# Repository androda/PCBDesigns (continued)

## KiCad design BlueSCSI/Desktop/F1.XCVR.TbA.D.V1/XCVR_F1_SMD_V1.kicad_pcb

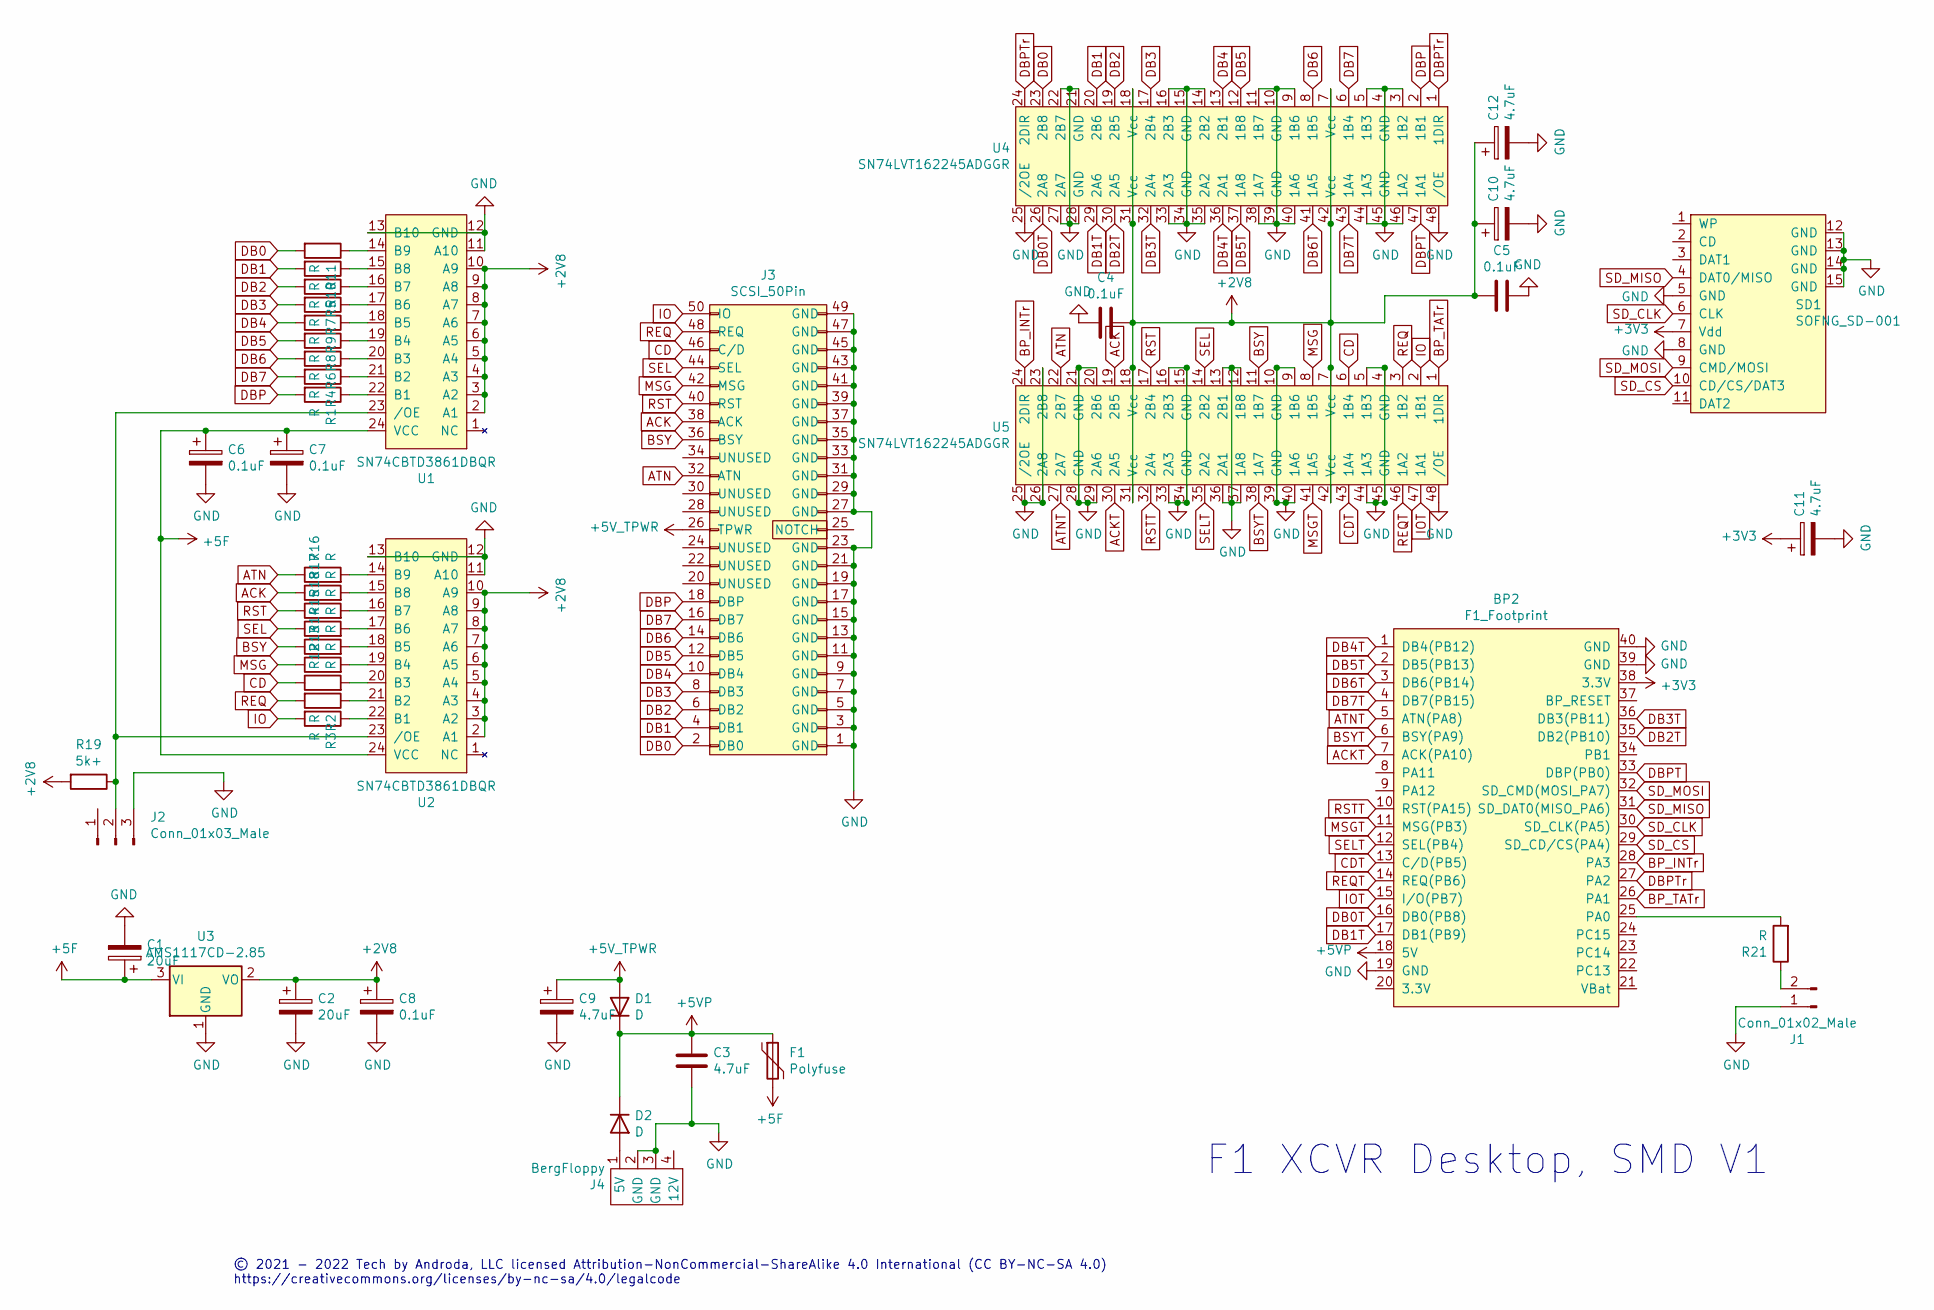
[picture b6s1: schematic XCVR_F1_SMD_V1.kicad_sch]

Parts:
BP2: F1_Footprint; BluePillModule
C1, C2: 20uF; C_1206_3216Metric_Pad1.42x1.75mm_HandSolder
C3, C9, C10, C11, C12: 4.7uF; C_0805_2012Metric_Pad1.15x1.40mm_HandSolder
C4, C5, C6, C7, C8: 0.1uF; C_0805_2012Metric_Pad1.15x1.40mm_HandSolder
D1, D2: D; D_SMA
F1: Polyfuse; Fuse_BelFuse_0ZRE0005FF_L8.3mm_W3.8mm
J1: Conn_01x02_Male; PinHeader_1x02_P2.54mm_Vertical
J2: Conn_01x03_Male; PinHeader_1x03_P2.54mm_Vertical
J3: SCSI_50Pin; SCSI50_EdgeConn
J4: BergFloppy; BergFloppy_RightAngle
R1, R2, R3, R4, R5, R6, R7, R8, R9, R10, R11, R12, R13, R14, R15, R16, R17, R18: R; R_0603_1608Metric_Pad1.05x0.95mm_HandSolder
R19: 5k+; R_0805_2012Metric_Pad1.15x1.40mm_HandSolder
R21: R; R_0805_2012Metric_Pad1.15x1.40mm_HandSolder
SD1: SOFNG_SD-001
U1, U2: SN74CBTD3861DBQR; SSOP-24_3.9x8.7mm_P0.635mm
U3: AMS1117CD-2.85; SOT-223-3_TabPin2
U4, U5: SN74LVT162245ADGGR; TSSOP-48_6.1x12.5mm_P0.5mm

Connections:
+2V8: C2.1, C4.1, C5.1, C8.1, C10.1, C12.1, R19.2, U1.2 (A1), U1.3 (A2), U1.4 (A3), U1.5 (A4), U1.6 (A5), U1.7 (A6), U1.8 (A7), U1.9 (A8), U1.10 (A9), U2.2 (A1), U2.3 (A2), U2.4 (A3), U2.5 (A4), U2.6 (A5), U2.7 (A6), U2.8 (A7), U2.9 (A8), U2.10 (A9), U3.2 (VO), U4.7 (Vcc), U4.18 (Vcc), U4.31 (Vcc), U4.42 (Vcc), U5.7 (Vcc), U5.18 (Vcc), U5.31 (Vcc), U5.42 (Vcc)
+3V3: BP2.38 (3.3V), C11.1, SD1.7 (Vdd)
+5F: C1.1, C6.1, C7.1, F1.2, U1.24 (VCC), U2.24 (VCC), U3.3 (VI)
+5V: C9.1, D1.2 (A), J3.26 (TPWR)
+5VP: BP2.18 (5V), C3.1, D1.1 (K), D2.1 (K), F1.1
ACK: J3.38 (ACK), R17.1, U5.19 (2B5)
ACKT: BP2.7 (ACK(PA10)), U5.30 (2A5)
ATN: J3.32 (ATN), R16.1, U5.22 (2B7)
ATNT: BP2.5 (ATN(PA8)), U5.27 (2A7)
BP_INTr: BP2.28 (PA3), U5.24 (2DIR)
BP_TATr: BP2.26 (PA1), U5.1 (1DIR)
BSY: J3.36 (BSY), R14.1, U5.11 (1B7)
BSYT: BP2.6 (BSY(PA9)), U5.38 (1A7)
CD: J3.46 (C/D), R12.1, U5.6 (1B4)
CDT: BP2.13 (C/D(PB5)), U5.43 (1A4)
DB0: J3.2 (DB0), R11.2, U4.23 (2B8)
DB0T: BP2.16 (DB0(PB8)), U4.26 (2A8)
DB1: J3.4 (DB1), R10.2, U4.20 (2B6)
DB1T: BP2.17 (DB1(PB9)), U4.29 (2A6)
DB2: J3.6 (DB2), R5.2, U4.19 (2B5)
DB2T: BP2.35 (DB2(PB10)), U4.30 (2A5)
DB3: J3.8 (DB3), R7.2, U4.17 (2B4)
DB3T: BP2.36 (DB3(PB11)), U4.32 (2A4)
DB4: J3.10 (DB4), R9.2, U4.13 (2B1)
DB4T: BP2.1 (DB4(PB12)), U4.36 (2A1)
DB5: J3.12 (DB5), R8.2, U4.12 (1B8)
DB5T: BP2.2 (DB5(PB13)), U4.37 (1A8)
DB6: J3.14 (DB6), R6.2, U4.8 (1B5)
DB6T: BP2.3 (DB6(PB14)), U4.41 (1A5)
DB7: J3.16 (DB7), R4.2, U4.6 (1B4)
DB7T: BP2.4 (DB7(PB15)), U4.43 (1A4)
DBP: J3.18 (DBP), R1.2, U4.2 (1B1)
DBPT: BP2.33 (DBP(PB0)), U4.47 (1A1)
DBPTr: BP2.27 (PA2), U4.1 (1DIR), U4.24 (2DIR)
GND: BP2.19 (GND), BP2.39 (GND), BP2.40 (GND), C1.2, C2.2, C3.2, C4.2, C5.2, C6.2, C7.2, C8.2, C9.2, C10.2, C11.2, C12.2, J1.1, J2.3, J3.1 (GND), J3.3 (GND), J3.5 (GND), J3.7 (GND), J3.9 (GND), J3.11 (GND), J3.13 (GND), J3.15 (GND), J3.17 (GND), J3.19 (GND), J3.21 (GND), J3.23 (GND), J3.27 (GND), J3.29 (GND), J3.31 (GND), J3.33 (GND), J3.35 (GND), J3.37 (GND), J3.39 (GND), J3.41 (GND), J3.43 (GND), J3.45 (GND), J3.47 (GND), J3.49 (GND), J4.2 (GND), J4.3 (GND), SD1.5 (GND), SD1.8 (GND), SD1.12 (GND), SD1.13 (GND), SD1.14 (GND), SD1.15 (GND), U1.11 (A10), U1.12 (GND), U1.13 (B10), U2.11 (A10), U2.12 (GND), U2.13 (B10), U3.1 (GND), U4.3 (1B2), U4.4 (GND), U4.5 (1B3), U4.9 (1B6), U4.10 (GND), U4.11 (1B7), U4.14 (2B2), U4.15 (GND), U4.16 (2B3), U4.21 (GND), U4.22 (2B7), U4.25 (/2OE), U4.27 (2A7), U4.28 (GND), U4.33 (2A3), U4.34 (GND), U4.35 (2A2), U4.38 (1A7), U4.39 (GND), U4.40 (1A6), U4.44 (1A3), U4.45 (GND), U4.46 (1A2), U4.48 (/OE), U5.4 (GND), U5.5 (1B3), U5.9 (1B6), U5.10 (GND), U5.12 (1B8), U5.13 (2B1), U5.15 (GND), U5.16 (2B3), U5.20 (2B6), U5.21 (GND), U5.23 (2B8), U5.25 (/2OE), U5.26 (2A8), U5.28 (GND), U5.29 (2A6), U5.33 (2A3), U5.34 (GND), U5.36 (2A1), U5.37 (1A8), U5.39 (GND), U5.40 (1A6), U5.44 (1A3), U5.45 (GND), U5.48 (/OE)
IO: J3.50 (IO), R3.2, U5.2 (1B1)
IOT: BP2.15 (I/O(PB7)), U5.47 (1A1)
MSG: J3.42 (MSG), R13.1, U5.8 (1B5)
MSGT: BP2.11 (MSG(PB3)), U5.41 (1A5)
unnamed: BP2.25 (PA0), R21.2
unnamed: D2.2 (A), J4.1 (5V)
unnamed: J1.2, R21.1
unnamed: J2.2, R19.1, U1.23 (/OE), U2.23 (/OE)
unnamed: R1.1, U1.22 (B1)
unnamed: R2.1, U2.21 (B2)
unnamed: R3.1, U2.22 (B1)
unnamed: R4.1, U1.21 (B2)
unnamed: R5.1, U1.16 (B7)
unnamed: R6.1, U1.20 (B3)
unnamed: R7.1, U1.17 (B6)
unnamed: R8.1, U1.19 (B4)
unnamed: R9.1, U1.18 (B5)
unnamed: R10.1, U1.15 (B8)
unnamed: R11.1, U1.14 (B9)
unnamed: R12.2, U2.20 (B3)
unnamed: R13.2, U2.19 (B4)
unnamed: R14.2, U2.18 (B5)
unnamed: R15.2, U2.17 (B6)
unnamed: R16.2, U2.14 (B9)
unnamed: R17.2, U2.15 (B8)
unnamed: R18.2, U2.16 (B7)
REQ: J3.48 (REQ), R2.2, U5.3 (1B2)
REQT: BP2.14 (REQ(PB6)), U5.46 (1A2)
RST: J3.40 (RST), R18.1, U5.17 (2B4)
RSTT: BP2.10 (RST(PA15)), U5.32 (2A4)
SD_CLK: BP2.30 (SD_CLK(PA5)), SD1.6 (CLK)
SD_CS: BP2.29 (SD_CD/CS(PA4)), SD1.10 (CD/CS/DAT3)
SD_MISO: BP2.31 (SD_DAT0(MISO_PA6)), SD1.4 (DAT0/MISO)
SD_MOSI: BP2.32 (SD_CMD(MOSI_PA7)), SD1.9 (CMD/MOSI)
SEL: J3.44 (SEL), R15.1, U5.14 (2B2)
SELT: BP2.12 (SEL(PB4)), U5.35 (2A2)

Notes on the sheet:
© 2021 - 2022 Tech by Androda, LLC licensed Attribution-NonCommercial-ShareAlike 4.0 International (CC BY-NC-SA 4.0) https://creativecommons.org/licenses/by-nc-sa/4.0/legalcode
F1 XCVR Desktop, SMD V1

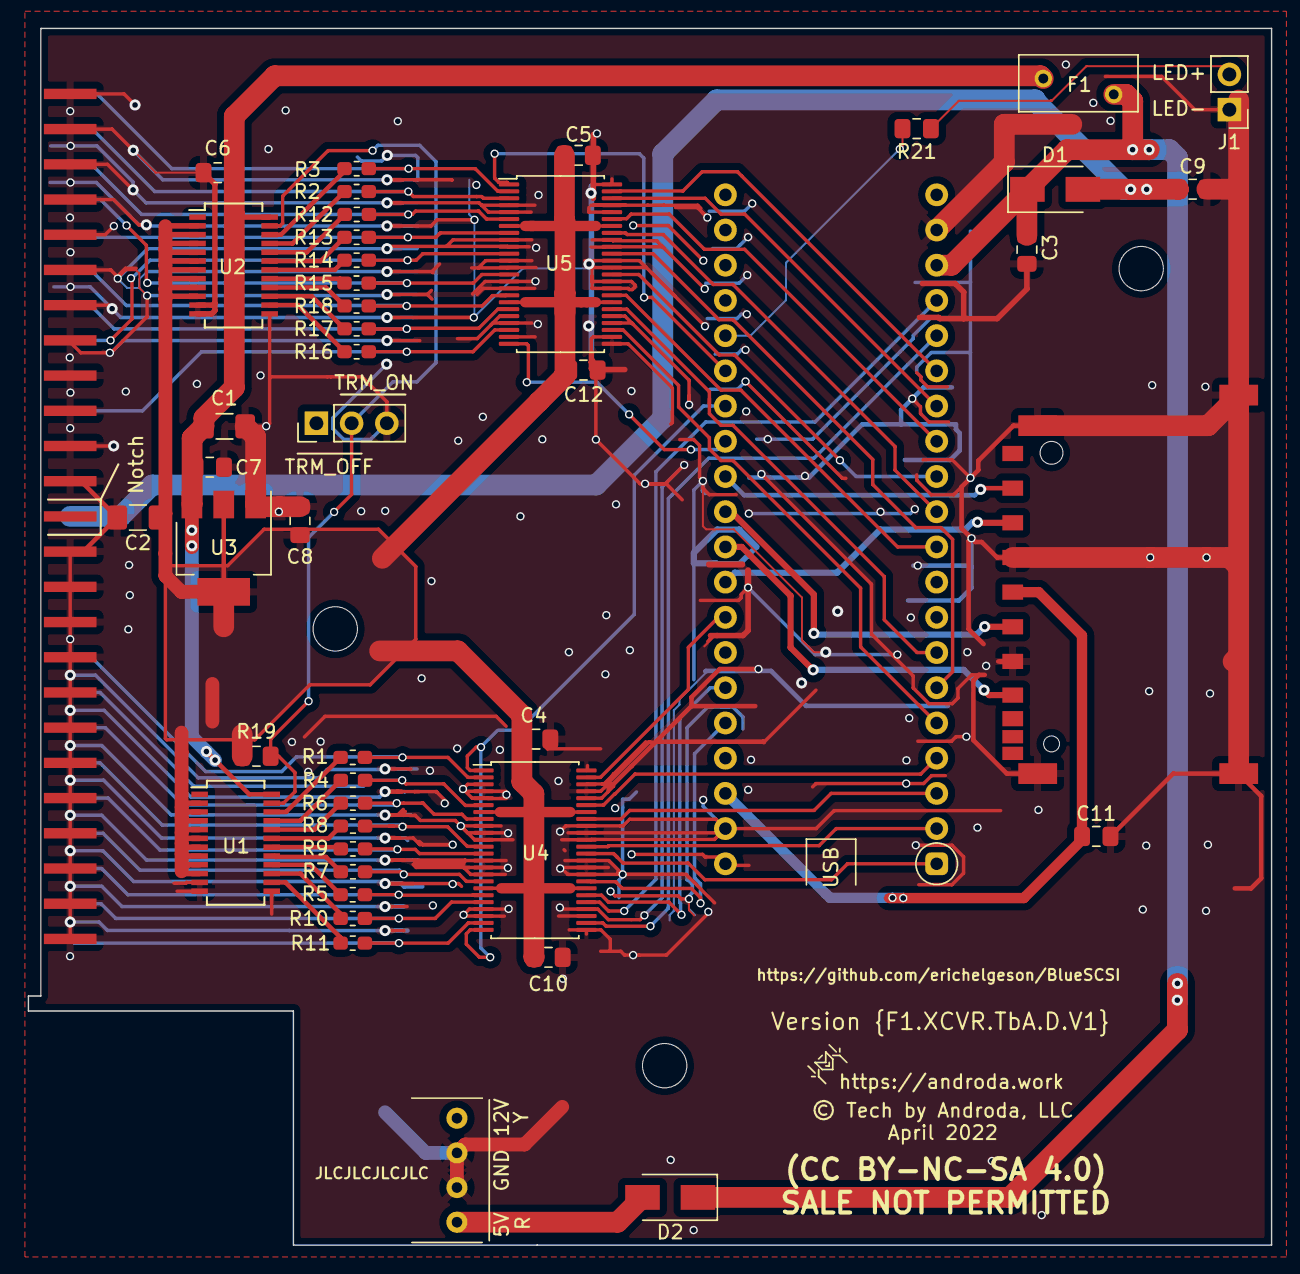
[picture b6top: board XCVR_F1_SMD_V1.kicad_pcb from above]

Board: 2 copper layers, 89.7 x 87.8 mm, 46 parts (0 on the bottom side), 71 nets.

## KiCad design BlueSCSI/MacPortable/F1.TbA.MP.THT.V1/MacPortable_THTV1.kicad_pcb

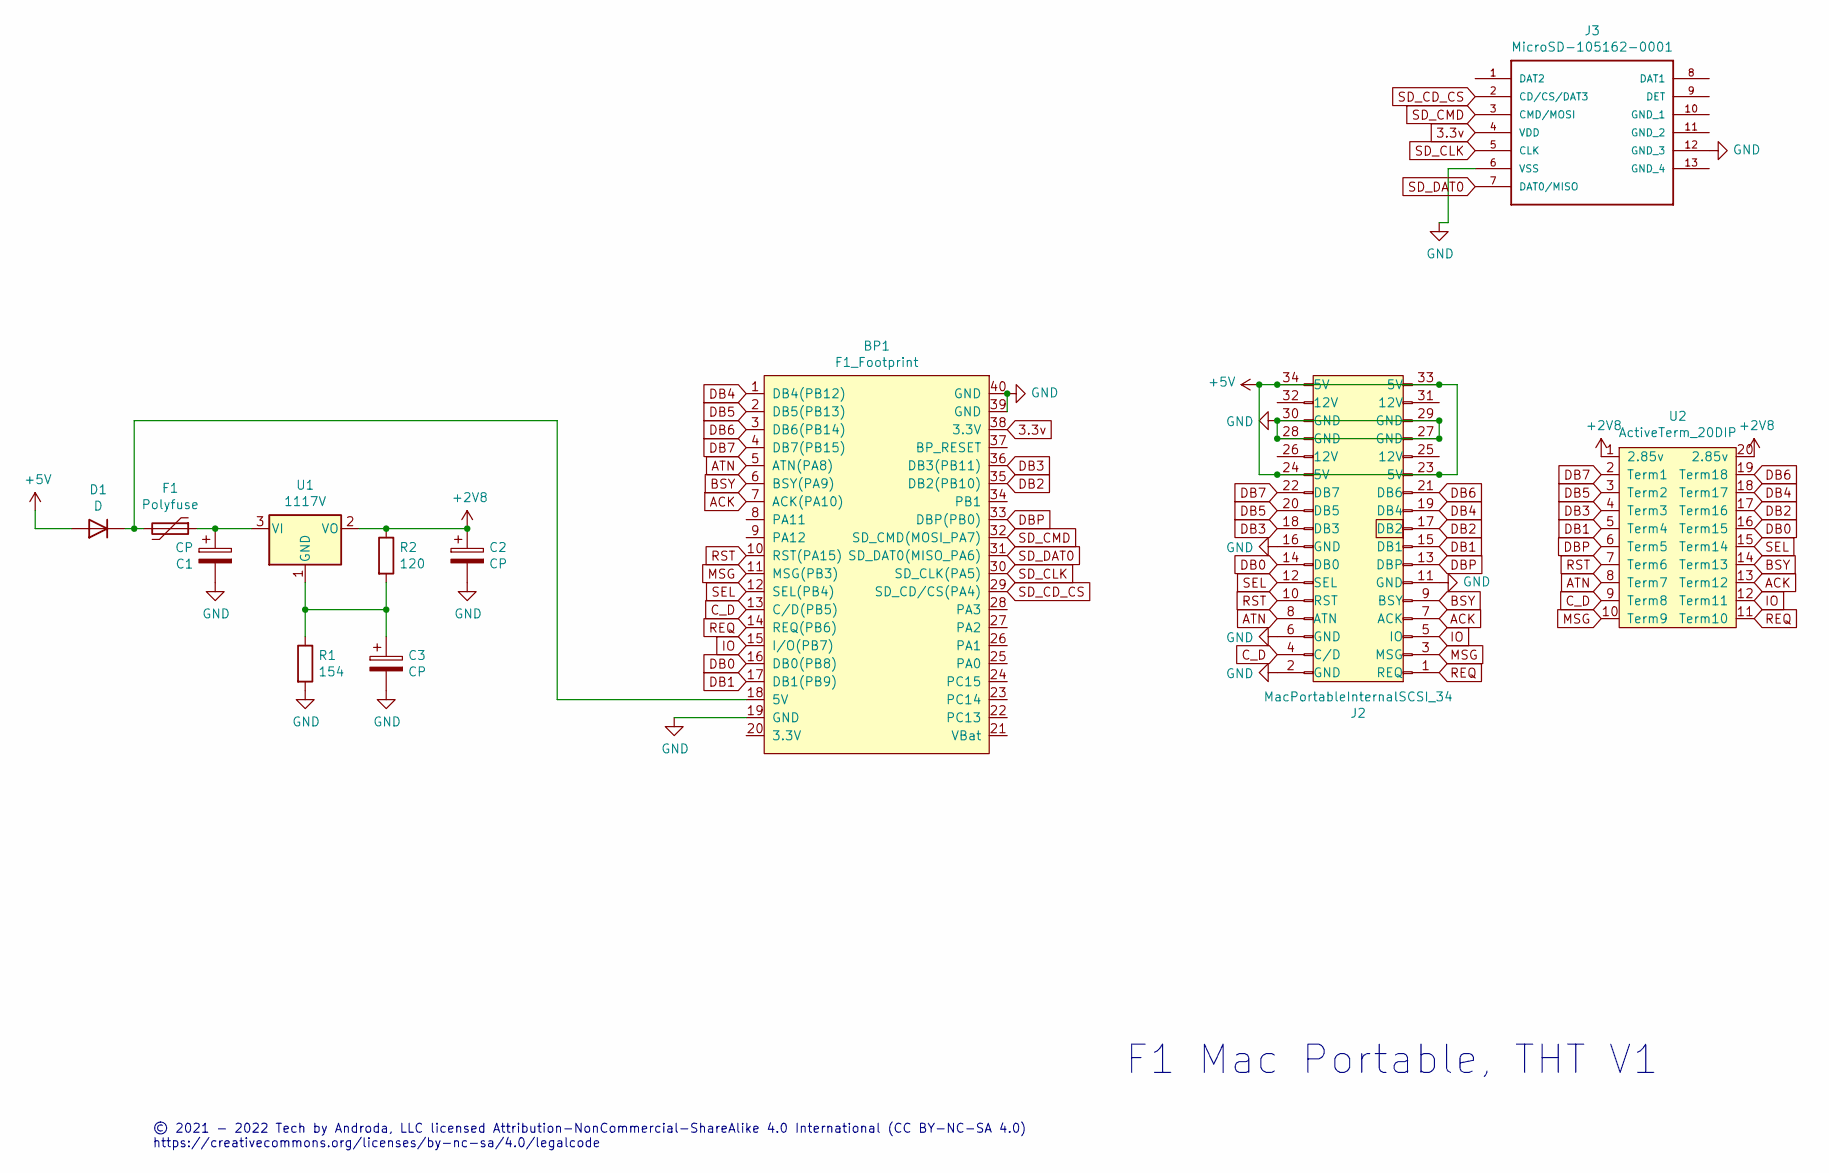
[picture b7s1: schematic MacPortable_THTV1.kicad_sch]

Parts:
BP1: F1_Footprint; BluePillModule
C1, C2, C3: CP; C_1206_3216Metric_Pad1.42x1.75mm_HandSolder
D1: D; D_A-405_P10.16mm_Horizontal
F1: Polyfuse; Fuse_BelFuse_0ZRE0005FF_L8.3mm_W3.8mm
J2: MacPortableInternalSCSI_34; PinHeader_2x17_P2.54mm_Vertical
J3: MicroSD-105162-0001; microsd_molex_1051620001; MANUFACTURER_PART_NUMBER 105162-0001; MOUSER_PART_NUMBER 538-105162-0001
R1: 154; R_Axial_DIN0207_L6.3mm_D2.5mm_P10.16mm_Horizontal
R2: 120; R_Axial_DIN0204_L3.6mm_D1.6mm_P5.08mm_Vertical
U1: 1117V; TO-220-3_Horizontal_TabDown
U2: ActiveTerm_20DIP; DIP-20_W7.62mm_Socket

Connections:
3.3v: BP1.38 (3.3V), J3.4 (VDD)
+2V8: C2.1, R2.1, U1.2 (VO), U2.1 (2.85v), U2.20 (2.85v)
+5V: D1.2 (A), J2.23 (5V), J2.24 (5V), J2.33 (5V), J2.34 (5V)
ACK: BP1.7 (ACK(PA10)), J2.7 (ACK), U2.13 (Term12)
ATN: BP1.5 (ATN(PA8)), J2.8 (ATN), U2.8 (Term7)
BSY: BP1.6 (BSY(PA9)), J2.9 (BSY), U2.14 (Term13)
C_D: BP1.13 (C/D(PB5)), J2.4 (C/D), U2.9 (Term8)
DB0: BP1.16 (DB0(PB8)), J2.14 (DB0), U2.16 (Term15)
DB1: BP1.17 (DB1(PB9)), J2.15 (DB1), U2.5 (Term4)
DB2: BP1.35 (DB2(PB10)), J2.17 (DB2), U2.17 (Term16)
DB3: BP1.36 (DB3(PB11)), J2.18 (DB3), U2.4 (Term3)
DB4: BP1.1 (DB4(PB12)), J2.19 (DB4), U2.18 (Term17)
DB5: BP1.2 (DB5(PB13)), J2.20 (DB5), U2.3 (Term2)
DB6: BP1.3 (DB6(PB14)), J2.21 (DB6), U2.19 (Term18)
DB7: BP1.4 (DB7(PB15)), J2.22 (DB7), U2.2 (Term1)
DBP: BP1.33 (DBP(PB0)), J2.13 (DBP), U2.6 (Term5)
GND: BP1.19 (GND), BP1.39 (GND), BP1.40 (GND), C1.2, C2.2, C3.2, J2.2 (GND), J2.6 (GND), J2.11 (GND), J2.16 (GND), J2.27 (GND), J2.28 (GND), J2.29 (GND), J2.30 (GND), J3.6 (VSS), J3.12 (GND_3), R1.2
IO: BP1.15 (I/O(PB7)), J2.5 (IO), U2.12 (Term11)
MSG: BP1.11 (MSG(PB3)), J2.3 (MSG), U2.10 (Term9)
unnamed: BP1.18 (5V), D1.1 (K), F1.2
unnamed: C1.1, F1.1, U1.3 (VI)
unnamed: C3.1, R1.1, R2.2, U1.1 (GND)
REQ: BP1.14 (REQ(PB6)), J2.1 (REQ), U2.11 (Term10)
RST: BP1.10 (RST(PA15)), J2.10 (RST), U2.7 (Term6)
SD_CD_CS: BP1.29 (SD_CD/CS(PA4)), J3.2 (CD/CS/DAT3)
SD_CLK: BP1.30 (SD_CLK(PA5)), J3.5 (CLK)
SD_CMD: BP1.32 (SD_CMD(MOSI_PA7)), J3.3 (CMD/MOSI)
SD_DAT0: BP1.31 (SD_DAT0(MISO_PA6)), J3.7 (DAT0/MISO)
SEL: BP1.12 (SEL(PB4)), J2.12 (SEL), U2.15 (Term14)

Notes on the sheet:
© 2021 - 2022 Tech by Androda, LLC licensed Attribution-NonCommercial-ShareAlike 4.0 International (CC BY-NC-SA 4.0) https://creativecommons.org/licenses/by-nc-sa/4.0/legalcode
F1 Mac Portable, THT V1

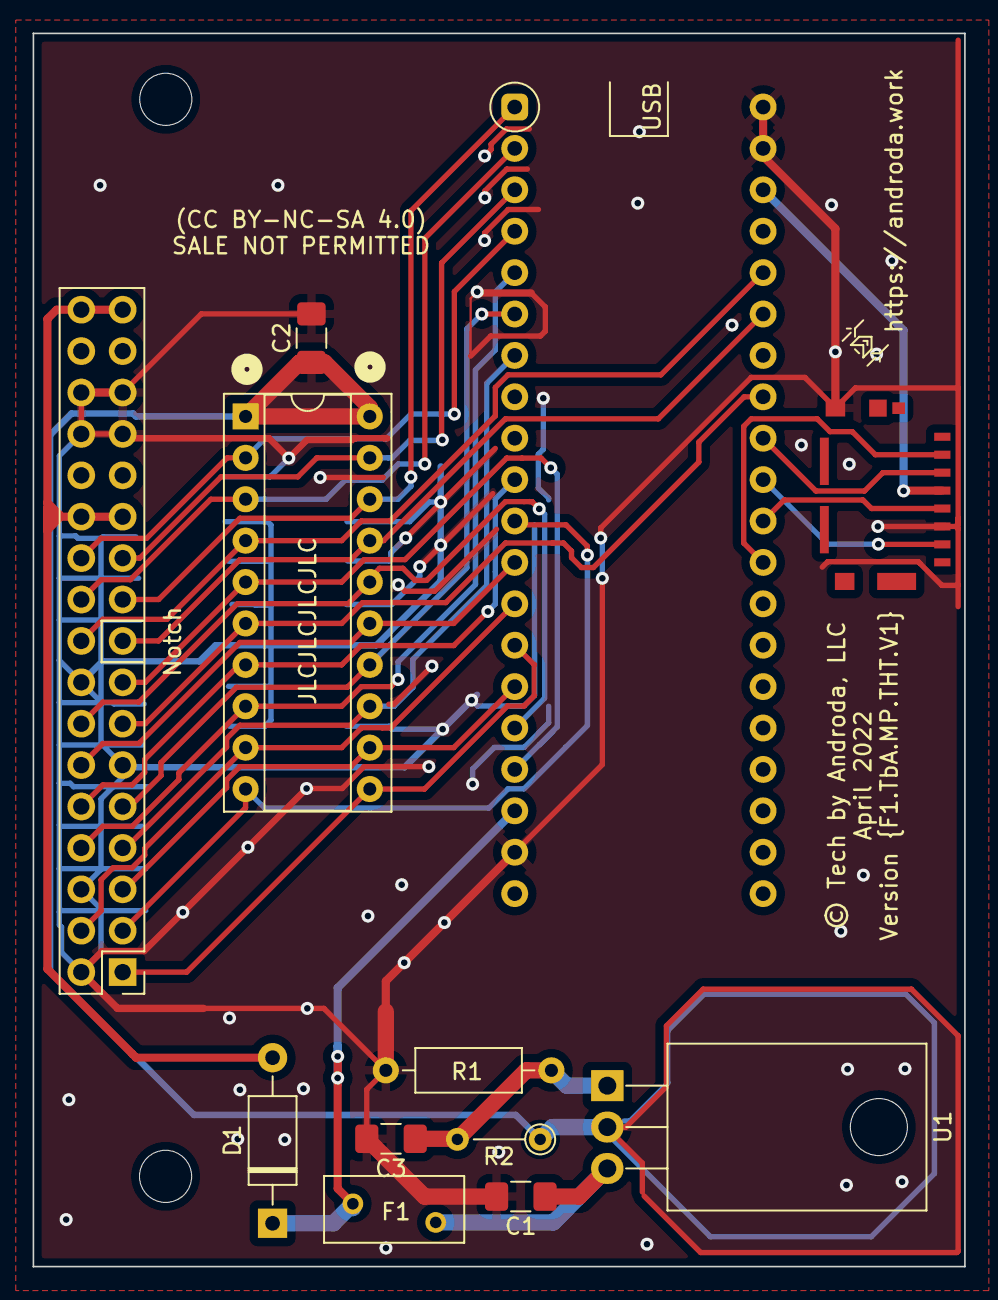
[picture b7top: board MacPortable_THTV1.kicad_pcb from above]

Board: 2 copper layers, 57.2 x 75.7 mm, 12 parts (0 on the bottom side), 29 nets.

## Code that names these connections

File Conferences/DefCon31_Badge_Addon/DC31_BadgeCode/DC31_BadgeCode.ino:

/*
 * Copyright Tech by Androda, LLC
 * July 2023
 * 
 */

#include <Adafruit_SHTC3.h>

// So many overrides
#include "hal_conf_custom.h"

#define SDA PB_11
#define SCL PB_10

Adafruit_SHTC3 sht = Adafruit_SHTC3();  // https://github.com/adafruit/Adafruit_SHTC3/blob/master/examples/SHTC3test/SHTC3test.ino

#define RED PA8
#define GREEN PA9
#define BLUE PA10

HardwareTimer timer1(TIM1);
uint32_t channelRed = STM_PIN_CHANNEL(pinmap_function(digitalPinToPinName(RED), PinMap_PWM));
uint32_t channelGreen = STM_PIN_CHANNEL(pinmap_function(digitalPinToPinName(GREEN), PinMap_PWM));
uint32_t channelBlue = STM_PIN_CHANNEL(pinmap_function(digitalPinToPinName(BLUE), PinMap_PWM));

#define HAL_I2C_MODULE_ENABLED

/*
 * PA8 is Red
 * PA9 is Green
 * PA10 is Blue
 * 
 * PB10 is SCL
 * PB11 is SDA
 * 
 * Serial output is PA2
 */

// Even more overrides
const PinMap PinMap_I2C_SDA[] = {
  {PB_7,  I2C1, STM_PIN_DATA(STM_MODE_AF_OD, GPIO_NOPULL, GPIO_AF1_I2C1)},
  {PB_9,  I2C1, STM_PIN_DATA(STM_MODE_AF_OD, GPIO_NOPULL, GPIO_AF1_I2C1)},
  {PB_11, I2C2, STM_PIN_DATA(STM_MODE_AF_OD, GPIO_PULLUP, GPIO_AF1_I2C2)},
  {PF_7,  I2C2, STM_PIN_DATA(STM_MODE_AF_OD, GPIO_NOPULL, GPIO_AF_NONE)},
  {NC,    NP,   0}
};
const PinMap PinMap_I2C_SCL[] = {
  {PB_6,  I2C1, STM_PIN_DATA(STM_MODE_AF_OD, GPIO_NOPULL, GPIO_AF1_I2C1)},
  {PB_8,  I2C1, STM_PIN_DATA(STM_MODE_AF_OD, GPIO_NOPULL, GPIO_AF1_I2C1)},
  {PB_10, I2C2, STM_PIN_DATA(STM_MODE_AF_OD, GPIO_PULLUP, GPIO_AF1_I2C2)},
  {PF_6,  I2C2, STM_PIN_DATA(STM_MODE_AF_OD, GPIO_NOPULL, GPIO_AF_NONE)},
  {NC,    NP,   0}
};


void SystemClock_Config(void)
{
  RCC_OscInitTypeDef RCC_OscInitStruct = {};
  RCC_ClkInitTypeDef RCC_ClkInitStruct = {};
  RCC_PeriphCLKInitTypeDef RCC_PeriphClkInit = {};

  /** Initializes the RCC Oscillators according to the specified parameters
  * in the RCC_OscInitTypeDef structure.
  */
  RCC_OscInitStruct.OscillatorType = RCC_OSCILLATORTYPE_HSI;
  RCC_OscInitStruct.HSIState = RCC_HSI_ON;
  RCC_OscInitStruct.HSICalibrationValue = RCC_HSICALIBRATION_DEFAULT;
  RCC_OscInitStruct.PLL.PLLState = RCC_PLL_OFF;
  RCC_OscInitStruct.PLL.PREDIV = RCC_PREDIV_DIV1;
  // Enable the LSI for use with RCC and wake interrupts
  RCC_OscInitStruct.OscillatorType = RCC_OSCILLATORTYPE_LSI;
  RCC_OscInitStruct.PLL.PLLState = RCC_PLL_NONE;
  RCC_OscInitStruct.LSIState = RCC_LSI_ON;
  if (HAL_RCC_OscConfig(&RCC_OscInitStruct) != HAL_OK) {
    Error_Handler();
  }
  /** Initializes the CPU, AHB and APB buses clocks
  */
  RCC_ClkInitStruct.ClockType = RCC_CLOCKTYPE_HCLK | RCC_CLOCKTYPE_SYSCLK
                                | RCC_CLOCKTYPE_PCLK1;
  RCC_ClkInitStruct.SYSCLKSource = RCC_SYSCLKSOURCE_HSI;
  RCC_ClkInitStruct.AHBCLKDivider = RCC_SYSCLK_DIV1;
  RCC_ClkInitStruct.APB1CLKDivider = RCC_HCLK_DIV1;

  if (HAL_RCC_ClockConfig(&RCC_ClkInitStruct, FLASH_LATENCY_1) != HAL_OK) {
    Error_Handler();
  }
}

void setup() {
  digitalWrite(SDA, 1);
  digitalWrite(SCL, 1);
  pinMode(SDA, OUTPUT);
  pinMode(SCL, OUTPUT);

  pinMode(RED, OUTPUT_OPEN_DRAIN);
  pinMode(GREEN, OUTPUT_OPEN_DRAIN);
  pinMode(BLUE, OUTPUT_OPEN_DRAIN);
  digitalWrite(RED, 1);
  digitalWrite(GREEN, 1);
  digitalWrite(BLUE, 1);

  Serial.begin(9600);

  Wire.setSDA(SDA);
  Wire.setSCL(SCL);
  Wire.begin();
  
  digitalWrite(RED, 1);
  digitalWrite(GREEN, 1);
  digitalWrite(BLUE, 1);
  Serial.println("");
  Serial.println("-----------------");
  if (sht.begin()) {
    // Flash green twice
    Serial.println("SHT Init Good");
    digitalWrite(RED, 1);
    digitalWrite(GREEN, 1);
    digitalWrite(BLUE, 1);
    digitalWrite(GREEN, 0);
    delay(5);
    digitalWrite(GREEN, 1);
  } else {
    // Flash red every second
    Serial.println("SHT Init Fail");
    digitalWrite(RED, 1);
    digitalWrite(GREEN, 1);
    digitalWrite(BLUE, 1);
    while(true) {
      digitalWrite(RED, 1);
      delay(2000);
      digitalWrite(RED, 0);
      delay(15);
      if (sht.begin()) {
        Serial.println("SHT Init Retry Good");
        break;
      }
      Serial.println("SHT Init Retry Fail");
    }
  }

  pwmRun();
  pwmStop();

  //// Set up one-second interrupts
  TIM_TypeDef *Instance = TIM6;
  HardwareTimer *MyTim = new HardwareTimer(Instance);
  MyTim->setMode(2, TIMER_OUTPUT_COMPARE);
  MyTim->setOverflow(1, HERTZ_FORMAT);
  MyTim->attachInterrupt(hardwareTimerWake);
  MyTim->resume();

  // Sleep
  HAL_PWR_EnterSLEEPMode(42, PWR_SLEEPENTRY_WFI);
}

void hardwareTimerWake() {
  sensors_event_t humidity, temp;
  sht.sleep(true);
  delay(10);
  sht.sleep(false);
  if (sht.getEvent(&humidity, &temp)) {
    double heatIndex = calculateHeatIndex(humidity, temp);
    showHeatIndexOnLed(heatIndex);
  } else {
    pwmRun();
    pwmRed();
    delay(10);
    pwmStop();
  }
  // Sleep
  HAL_PWR_EnterSLEEPMode(42, PWR_SLEEPENTRY_WFI);
}

void showHeatIndexOnLed(double heatIndex) {
  /*
   * Category barriers:
   * < 80 after HI conversion, not in the caution zone at all
   * 80 to 90 is Caution
   * > 90 and < 104 is Extreme Caution
   * 104 to 125 is Danger
   * > 125 is Extreme Danger
   */
   if (heatIndex < 80) {
    pwmBits(0x100, 10, 100, 10);  // Blue
    pwmStop();
   } else if (heatIndex < 90) {
    pwmBits(0x10, 10, 100, 25);  // Green
    pwmStop();
   } else if (heatIndex < 104) {
    pwmBits(0x11, 10, 100, 500);  // Yellow
    pwmStop();
   } else if (heatIndex < 125) {
    pwmBits(0x1, 10, 20, 700);  // Red
    pwmStop();
   } else {
    pwmBits(0x101, 10, 20, 1000);  // Purple
    pwmStop();
   }
}

void pwmBits(uint32_t bitsToPwm, uint32_t onDuration, uint32_t offDuration, uint32_t loops) {
  for (; loops > 0; loops--) {
    // ON
    WRITE_REG(TIM1->CCER, bitsToPwm);
    for (uint32_t spacer = onDuration;spacer > 0; spacer--) {
      asm("nop");
    }
    // OFF
    CLEAR_BIT(TIM1->CCER, 0xFFFFFFFF);
    for (uint32_t spacer = offDuration;spacer > 0; spacer--) {
      asm("nop");
    }
  }
}

double calculateHeatIndex(sensors_event_t humidity, sensors_event_t temp) {
  double degrees_f = (temp.temperature * 1.8) + 32;
  double rh = humidity.relative_humidity;
  double result;
  
  float simpleHeatIndex = 0.5D * (degrees_f + 61.0D + ((degrees_f - 68.0D) * 1.2D) + (rh * 0.094D));
  Serial.print("SHI: ");Serial.println(simpleHeatIndex);

  if (((simpleHeatIndex + degrees_f) / 2.0D) > 80) {
    float seg1 = -42.379F + (2.04901523F * degrees_f);
    float seg2 = (10.14333127F * rh);
    float seg3 = (0.22475541F * degrees_f * rh);
    float seg4 = (0.00683783D * degrees_f * degrees_f);
    float seg5 = (0.05481717D * rh * rh);
    float seg6 = (0.00122874D * degrees_f * degrees_f * rh);
    float seg7 = (0.00085282D * degrees_f * rh * rh);
    float seg8 = (0.00000199D * degrees_f * degrees_f * rh * rh);
    double heatIndex = double(seg1) + double(seg2) - double(seg3) - double(seg4) - double(seg5) + double(seg6) + double(seg7) - double(seg8);

    //  Adjustments
    if (rh < 13 && degrees_f > 80 && degrees_f < 112) {
      double adjustment = ((13 - rh) / 4) * sqrt((17 - abs(degrees_f - 95.0)) / 17);
      heatIndex = heatIndex - adjustment;
    }
  
    if (rh > 85 && degrees_f > 80 && degrees_f < 87) {
      double adjustment = (((rh - 85) / 10) * ((87 - degrees_f) / 5));
      heatIndex = heatIndex - adjustment;
    }
    result = heatIndex;
  }
  
  return result;
}

void pwmRun() {
  timer1.pause();
  timer1.setPWM(channelRed, RED, 500053, 500000);
  timer1.setPWM(channelGreen, GREEN, 799, 10);
  timer1.setPWM(channelBlue, BLUE, 599, 10);
}

void pwmRed() {
  // CCER bit 0 should be 1
  // All other CCER bits are 0
  WRITE_REG(TIM1->CCER, 0x1);
}

void pwmStop() {
  CLEAR_BIT(TIM1->CCER, 0xFFFFFFFF);
}

void loop() {
}

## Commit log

2021-03-20 License
2021-03-20 PowerBook board design
2021-03-20 Parts List
    The parts are pretty basic, assembly is the hard part
2021-04-10 PowerBook V2
2021-04-10 Wrong word
2021-05-22 Stick the license in every folder
    People may not realize what the license is unless it's everywhere. So put it everywhere.
2021-05-22 V3 PowerBook design
    And STLs for V2 that I forgot to upload
2021-05-22 Fix Typo
2021-06-01 Start creating Desktop design tree
2021-06-01 Fix Typo
    Beige G3 can't boot 7.5.3...
2021-06-01 Add Desktop design F1.V1
2021-06-03 Readme updates
2021-06-03 Still getting the hang of markdown
2021-06-15 Add STL for mounting bracket
2021-06-15 Create LICENSE for potable V0
2021-06-15 Add Portable V0
2021-07-01 Create License for Newton Internal Serial
2021-07-01 Newton Internal Serial
2021-09-27 Add license for PowerBook V4
2021-09-27 PowerBook Version 4
    A rather different design, all SMD
2021-10-01 Create license for 50 pin to 2.5 inch scsi adapter board
2021-10-01 Create 50 pin to 2.5 inch SCSI adapter board
2021-10-01 Add pictures
2021-11-18 Create folder for through-hole type desktop V1
2021-11-18 Update powerbook V4 to mention 1k resistors
2021-11-18 Through hole style desktop mainline V1
    Note the creative commons non-commercial license
2021-11-18 Add mounting bracket for desktop THT V1
2021-12-22 License for backlit screen upgrade
2021-12-22 Upgrade cable for original backlit portable
    This cable is part of the upgrade for an original non-backlit portable to use a backlit screen.
2022-04-12 Add Mac Portable V1
2022-04-15 F1 X
2022-09-15 Add old design files
2022-10-12 PCB Design for tashtrio from lampmerchant
2022-10-12 I'm bad at markdown
2022-10-21 Tested PS2_ADB V1 on Beige G3
2023-02-21 Update License
2023-02-21 LC Power Supply Options
2023-02-21 Be more blunt about the license
2023-08-19 DefCon 31 Badge Addon Design
2023-08-19 PCB Top Image
2023-08-19 Trying to add PCB Image
